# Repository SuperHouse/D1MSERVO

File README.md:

Servo Shield for the WeMos D1 Mini
==================================

Copyright 2016 SuperHouse Automation Pty Ltd  
SuperHouse site:  www.superhouse.tv  
SuperHouse email: info@superhouse.tv  

A 16-channel servo controller shield for the [WeMos D1 Mini][1] 
and other compatible boards based on the same header format.

Features:

 * 16 PWM output channels at 3.3V.
 * I2C interface with pull-up resistors.
 * Configurable I2C address to allow stacking. Default address 0x40.
 * PCA9685 PWM controller IC.
 * SCL: D1. SDA: D2.
 * External power terminals for powering servos at 6V.
 * Power jumper to link D1 Mini 5V rail to servo power.
 * OE (active low Output Enable) broken out for manual connection if required.
 * Power LED to show when servo power is available.

More information is available at:

  http://www.superhouse.tv/d1mservo

INSTALLATION
------------
The design is saved as an EAGLE project. EAGLE PCB design software is
available from www.cadsoftusa.com free for non-commercial use. To use
this project download it and place the directory containing these files
into the "eagle" directory on your computer.

DISTRIBUTION
------------
The specific terms of distribution of this project are governed by the
license referenced below.

LICENSE
-------
Licensed under the TAPR Open Hardware License (www.tapr.org/OHL).
The "license" folder within this repository also contains a copy of
this license in plain text format.

[1]: http://www.wemos.cc/wiki/doku.php?id=en:d1_mini

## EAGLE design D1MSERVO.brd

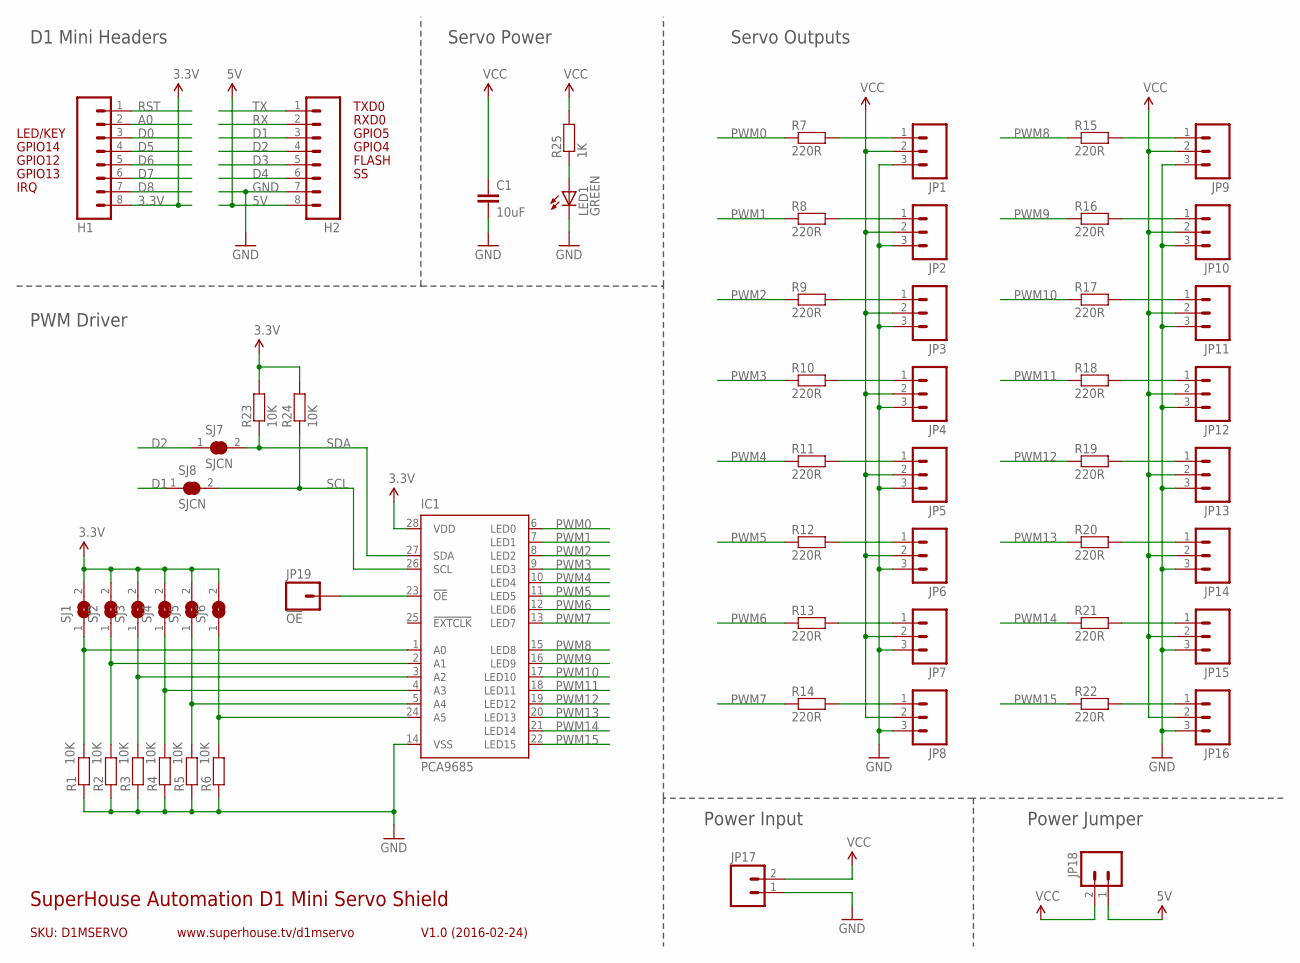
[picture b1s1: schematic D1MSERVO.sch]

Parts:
C1: 10uF; 0805
H1, H2: M08; 1X08
IC1: PCA9685; TSSOP28
JP1, JP2, JP3, JP4, JP5, JP6, JP7, JP8, JP9, JP10, JP11, JP12, JP13, JP14, JP15, JP16: M03PTH; 1X03
JP17: M023.5MM; SCREWTERMINAL-3.5MM-2
JP18: M02PTH; 1X02
JP19: !OE; 1X01
LED1: GREEN; LED-0603
R1, R2, R3, R4, R5, R6, R23, R24: 10K; 0603
R7, R8, R9, R10, R11, R12, R13, R14, R15, R16, R17, R18, R19, R20, R21, R22: 220R; 0603
R25: 1K; 0603
SJ1, SJ2, SJ3, SJ4, SJ5, SJ6: SJN; SJ
SJ7, SJ8: SJCN; SJC

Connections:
3.3V: H1.8, IC1.28 (VDD), R23.2, R24.2, SJ1.2, SJ2.2, SJ3.2, SJ4.2, SJ5.2, SJ6.2
5V: H2.8, JP18.1
A0: H1.2
D0: H1.3
D1: H2.3, SJ8.1
D2: H2.4, SJ7.1
D3: H2.5
D4: H2.6
D5: H1.4
D6: H1.5
D7: H1.6
D8: H1.7
GND: C1.2, H2.7, IC1.14 (VSS), JP1.3, JP2.3, JP3.3, JP4.3, JP5.3, JP6.3, JP7.3, JP8.3, JP9.3, JP10.3, JP11.3, JP12.3, JP13.3, JP14.3, JP15.3, JP16.3, JP17.1, LED1.C, R1.1, R2.1, R3.1, R4.1, R5.1, R6.1
unnamed: JP1.1, R7.2
unnamed: JP2.1, R8.2
unnamed: IC1.1 (A0), R1.2, SJ1.1
unnamed: IC1.2 (A1), R2.2, SJ2.1
unnamed: IC1.3 (A2), R3.2, SJ3.1
unnamed: IC1.4 (A3), R4.2, SJ4.1
unnamed: IC1.5 (A4), R5.2, SJ5.1
unnamed: IC1.24 (A5), R6.2, SJ6.1
unnamed: JP3.1, R9.2
unnamed: JP4.1, R10.2
unnamed: JP5.1, R11.2
unnamed: JP6.1, R12.2
unnamed: JP7.1, R13.2
unnamed: JP9.1, R15.2
unnamed: JP8.1, R14.2
unnamed: JP10.1, R16.2
unnamed: JP11.1, R17.2
unnamed: JP12.1, R18.2
unnamed: JP13.1, R19.2
unnamed: JP14.1, R20.2
unnamed: JP15.1, R21.2
unnamed: JP16.1, R22.2
unnamed: LED1.A, R25.1
unnamed: IC1.23 (!OE), JP19.1
PWM0: IC1.6 (LED0), R7.1
PWM1: IC1.7 (LED1), R8.1
PWM2: IC1.8 (LED2), R9.1
PWM3: IC1.9 (LED3), R10.1
PWM4: IC1.10 (LED4), R11.1
PWM5: IC1.11 (LED5), R12.1
PWM6: IC1.12 (LED6), R13.1
PWM7: IC1.13 (LED7), R14.1
PWM8: IC1.15 (LED8), R15.1
PWM9: IC1.16 (LED9), R16.1
PWM10: IC1.17 (LED10), R17.1
PWM11: IC1.18 (LED11), R18.1
PWM12: IC1.19 (LED12), R19.1
PWM13: IC1.20 (LED13), R20.1
PWM14: IC1.21 (LED14), R21.1
PWM15: IC1.22 (LED15), R22.1
RST: H1.1
RX: H2.2
SCL: IC1.26 (SCL), R24.1, SJ8.2
SDA: IC1.27 (SDA), R23.1, SJ7.2
TX: H2.1
VCC: C1.1, JP1.2, JP2.2, JP3.2, JP4.2, JP5.2, JP6.2, JP7.2, JP8.2, JP9.2, JP10.2, JP11.2, JP12.2, JP13.2, JP14.2, JP15.2, JP16.2, JP17.2, JP18.2, R25.2

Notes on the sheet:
FLASH
GPIO12
GPIO4
GPIO5
RXD0
TXD0
GPIO13
GPIO14
IRQ
LED/KEY
SKU: D1MSERVO
SuperHouse Automation D1 Mini Servo Shield
V1.0 (2016-02-24)
www.superhouse.tv/d1mservo
Servo Outputs
D1 Mini Headers
Power Input
PWM Driver
Power Jumper
Servo Power

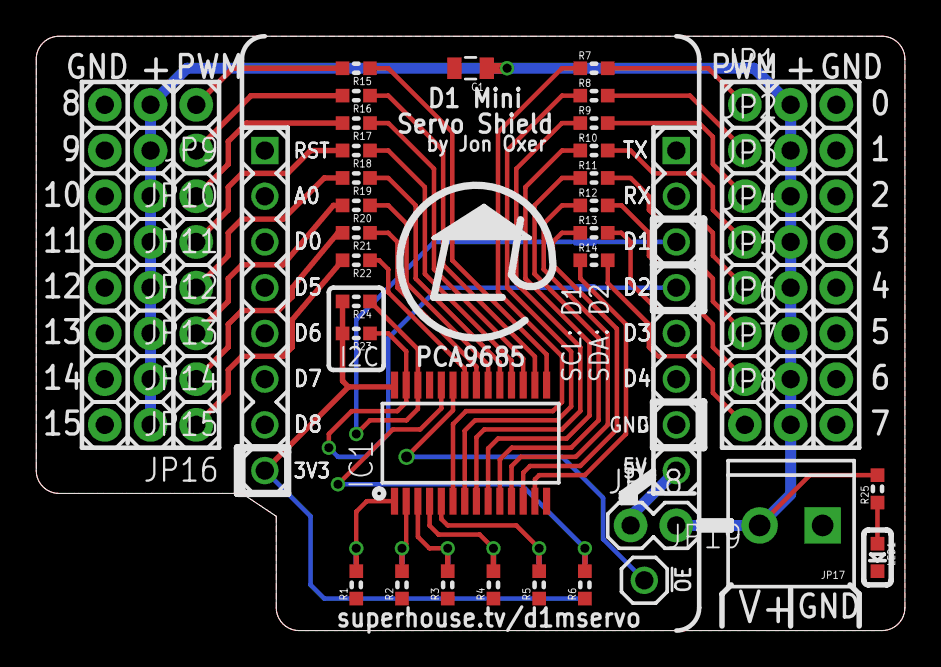
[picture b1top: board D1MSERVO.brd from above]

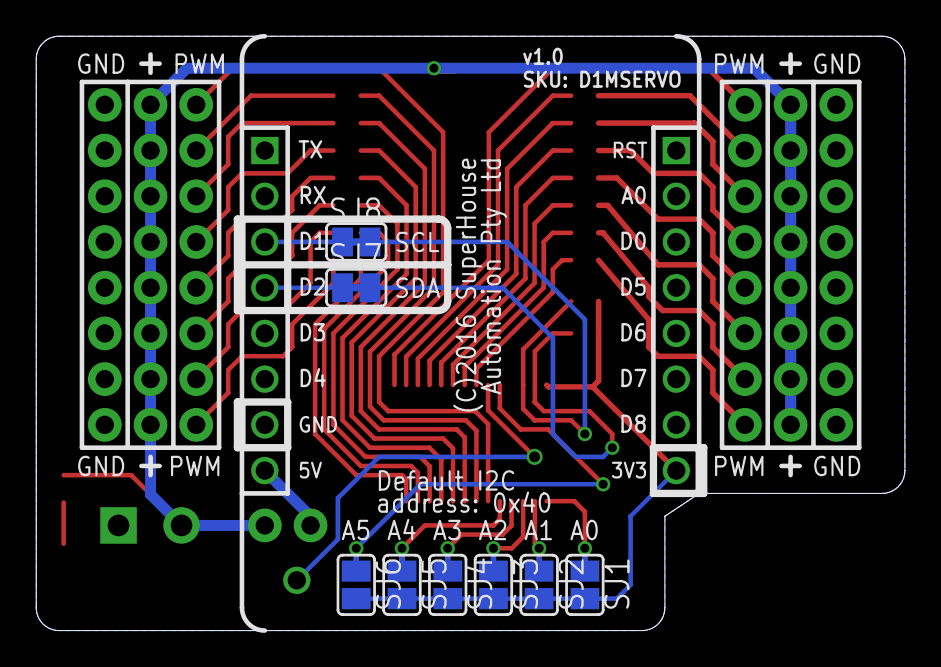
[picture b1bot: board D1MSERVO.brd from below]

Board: 2 copper layers, 48.3 x 33.0 mm, 57 parts (8 on the bottom side), 48 nets.

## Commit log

2016-02-26 Initial import
2016-02-26 Added license, preview images, and updated README
2016-02-26 Fixed syntax error
2016-02-26 Clarified description
2016-02-26 Changed I2C pins
2016-02-29 Changed I2C pins (again) to match ESP12E like on the D1 Mini and D1 R2
2016-03-03 Fixed silkscreen and preview images to reflect updated SCL and SDA pin assignments

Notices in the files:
D1MSERVO.brd:
(C)2016 SuperHouse
parts and their libraries:
freetronics-original: Licensing: CC v3.0 Share-Alike You are welcome to use this library for commercial purposes.
